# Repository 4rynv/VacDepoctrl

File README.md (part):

# VacDepoctrl — Vacuum Deposition Controller

A Raspberry Pi-based vacuum process controller. The current process is DC magnetron sputter deposition — chamber pump-down, argon gas flow, plasma ignition, and sputtering via a live Tkinter GUI with scrolling sensor graphs and a hardware-interlocked state machine. A thermal evaporation mode is planned as a second process on the same rig control stack.

---

## Table of Contents

- [Hardware Overview](#hardware-overview)
- [Software Architecture](#software-architecture)
- [File Structure](#file-structure)
- [State Machine](#state-machine)
- [Pressure Reference](#pressure-reference)
- [Installation](#installation)
- [Running](#running)
- [Remote GUI Access](#remote-gui-access)
- [Web Dashboard](#web-dashboard)
- [Simulation Mode](#simulation-mode)
- [Configuration](#configuration)
- [GUI Guide](#gui-guide)
- [Known Limitations](#known-limitations)
- [Roadmap](#roadmap)

---

## Hardware Overview

| Component | Model | Interface | Notes |
|---|---|---|---|
| Microcontroller | Raspberry Pi 5 (BCM GPIO) | — | Host for all control logic |
| Pirani gauge | ACE Instruments DHPG-015 | Analog 0–10V | Divided to 0–3.3V before ADC (ratio 0.33) |
| ADC | ADS1115 | **I2C bus 1** @ 0x48 | Pirani on A0 (divided), MFC feedback on A1 (divided), turbo RPM tach on A2 |
| MFC | MKS 1179A | Analog 0–5V setpoint | 0–700 sccm Argon |
| DAC | MCP4725 | **I2C bus 1** @ 0x60 | Level-shifted to the MFC's full 0–5V setpoint range — see below |
| DAC buffer | LM358P op-amp | Analog | Buffers + level-shifts the DAC output up to 0–5V; DAC alone cannot drive the MFC setpoint input |
| Turbo enable | Opto-isolator (4N35) | GPIO 17 (BCM, phys 11) | Marginal — needs BC547 output buffer, see below |
| MFC valve close | Emergency shut | GPIO 27 (BCM, phys 13) | Pulls MFC valve closed on demand |
| Turbo inlet valve | Relay via BC547 | **GPIO 22 (BCM, phys 15)** | HIGH = valve OPEN, LOW = valve CLOSED (relay NC contact) |
| Energy meter | PZEM-004T-100A | Modbus-RTU over CP2102 USB-TTL, `/dev/ttyUSB0` | AC voltage/current/power on the variac output; plasma-ignition sensing. **Optional at startup** — see below |

### Raspberry Pi pin connections

[Full 40-pin header and device wiring diagram](docs/pinout.md)

| Function | BCM GPIO | Physical header pin | Connection |
|---|---|---|---|
| I2C1 SDA | GPIO2 | **3** | ADS1115 SDA + MCP4725 SDA |
| I2C1 SCL | GPIO3 | **5** | ADS1115 SCL + MCP4725 SCL |
| Signal ground | — | **6** (or another GND) | ADC/DAC signal ground |
| Turbo enable | GPIO17 | **11** | Opto-isolator input circuit |
| MFC emergency close | GPIO27 | **13** | Existing MFC valve-close interface |
| Turbo inlet valve | GPIO22 | **15** | BC547 relay-driver input |

GPIO23/24 (physical pins 16/18) are no longer the I2C connection.

### I2C: Hardware Bus 1 on GPIO 2/3

The Pi 5 uses hardware I2C1 at 100 kHz. Configure `/boot/firmware/config.txt`:

```ini
dtparam=i2c_arm=on
dtparam=i2c_arm_baudrate=100000
```

| Signal | BCM | Physical pin |
|---|---|---|
| SDA | GPIO 2 | 3 |
| SCL | GPIO 3 | 5 |
| GND | Ground | 6 |

Connect both ADS1115 and MCP4725 to this bus; keep pull-ups at 3.3 V.
Power down before moving SDA/SCL from the previous GPIO23/24 wiring.
The code uses `ExtendedI2C(I2C_BUS_NUMBER)` with `I2C_BUS_NUMBER = 1`.
The older software-bus setup was a workaround for reported damaged GPIO2/3
on a previous setup; this configuration assumes functioning GPIO2/3.
Reboot after changing boot configuration; the operator performs device checks
and the first controller launch with equipment in a safe condition.

### Voltage Divider (Pirani Output)

The DHPG-015 outputs 0–10V. A 3-resistor voltage divider scales this to 0–3.3V for the ADS1115 (divider ratio 0.33). All pressure thresholds in `config.py` are expressed in post-divider (ADC-side) volts. The full manufacturer calibration table lives in `hardware/datasheets/Di-Hi-Pr-Pirani output voltage.pdf` and is transcribed as `_PIRANI_CAL` in `main.py`.

### DAC Output Buffer + Level Shifter (LM358P)

The MCP4725 cannot source enough current to drive the MFC setpoint input directly — above ~1.25V the output voltage collapses under load even though it reads correctly when unloaded. An LM358P stage buffers the DAC output and shifts it up to the MFC's full 0–5V setpoint range before it reaches the MFC (`ARGON_DAC_VREF = 5.0` in `config.py` reflects this — commanded flow covers the full 0–`MFC_FULL_SCALE` range, not a fraction of it):

```
DAC OUT ──────────────┬──── LM358 IN+ (pin 3)
                       │
                  (feedback) IN- (pin 2) ──── OUT (pin 1) ──── MFC setpoint
LM358 VCC (pin 8) ── Pi 5V
LM358 GND (pin 4) ── GND
```

Power the op-amp from the Pi's **5V** rail, not 3.3V. The diagram above shows the original current-buffer wiring; the gain-setting feedback network that shifts the output up to 0–5V isn't captured in this ASCII diagram.

### Turbo Inlet Valve (GPIO 22 → BC547 → Relay → Solenoid)

The turbo inlet solenoid valve (~50 mA @ 25–26 V) is switched by a relay, driven by a BC547:

```
GPIO22 ──470Ω── base   BC547   collector ── relay coil ── +5V
                          emitter ── GND         ▲
                                          1N4007 across coil
                                          (band toward +5V)

Valve circuit ── relay COM + NC contacts (isolated from the Pi)
```

- Valve is wired through the relay's **NC (normally closed)** contact: relay released = valve circuit shorted = **valve CLOSED**; relay energized = **valve OPEN**.
- Logic (in `_poll()`, `turbo_valve_step()`): valve held CLOSED at all times; **latched OPEN** during **VENTING** once turbo pump RPM (tach on ADC A2, see [Turbo Pump RPM](#turbo-pump-rpm-adc-a2)) sustains `TURBO_VALVE_CONFIRM_SAMPLES` consecutive reads at or below `TURBO_VALVE_OPEN_RPM_MAX` (35000 RPM); re-closed automatically on leaving VENTING. The debounce prevents a single corrupted I2C read from opening the valve; the latch prevents relay chatter once open. Driven by rotor speed directly rather than inferring it from chamber pressure — the earlier pressure-based gate (`TURBO_VALVE_OPEN_MBAR`) has been replaced.
- Fail-safe: if the Pi crashes or loses power, the relay releases and the valve **fails closed** — the safe direction for the turbo inlet.
- GUI shows live actuation state (`T-VALVE : CLOSED` / `OPEN (venting)`).

### Turbo Pump RPM (ADC A2)

- Tach/speed output, 0–3.3V linear = 0–90000 RPM (`TURBO_RPM_VOLTAGE_FULL_SCALE`, `TURBO_RPM_FULL_SCALE`), read by `TurboRPMController` (`turbo_rpm.py`) every poll tick regardless of state.
- Displayed in its own **Turbo Pump** panel (`T-RPM`, `T-RPM V`, a scrolling RPM graph, plus `OPTO` and `T-VALVE` state — both turbo-side actuators, moved here from the Pirani panel) — below the Plasma panel, beside the Pirani/MFC panels.
- During **VENTING**, once RPM drops to/below `VENTING_PUMP_OFF_PROMPT_RPM` (2000), the Pirani panel's status message turns orange and prompts the operator to turn off the primary/roughing pump — an early, informational cue, not a gate. The actual gate on completing the vent is separate — see [Vent Completion Confirmation](#vent-completion-confirmation) below.
- Feeds the turbo inlet valve interlock above and the cross-sensor checks below.

### Vent Completion Confirmation

Reaching atmospheric pressure during VENTING does **not** by itself complete the vent. Earlier, `sm.update()` transitioned `VENTING → IDLE` purely from Pirani voltage — but the turbo inlet valve closes the instant the state leaves VENTING (`turbo_valve_step()`), so that auto-transition could reclose the valve before the operator had any real chance to react to the "turn off the primary pump" cue above, let alone actually do it.

`VENTING → IDLE` is now owned exclusively by `_poll()` (the same ownership pattern as `ARGON_FLUSH → PLASMA_IGNITING`), gated by `vent_complete_ready()`: **both** atmospheric pressure **and** an explicit operator click are required.

- Once Pirani reaches `VENTING_COMPLETE_VOLTAGE` during VENTING, `_state["vent_complete_pending"]` latches True — the Pirani panel's status message turns red ("Atmosphere reached — turn OFF the primary/roughing pump, then click Confirm Pump Off") and a **Confirm Pump Off** button appears in Controls (hidden otherwise, same show/hide pattern as Clear Fault).
- Clicking it sets `_state["vent_complete_confirmed"]`; `_poll()` picks this up on its next tick and, if pressure is still at/above atmosphere, transitions to IDLE — closing the turbo inlet valve as part of the normal VENTING-exit path.
- Both flags reset on entering IDLE or VENTING (`handle_hardware_interlocks()`), so a stale confirmation from a previous cycle can never auto-complete the next one.

### Energy Meter (PZEM-004T-100A, plasma ignition sensing)

Reads AC voltage/current/power/energy/frequency/power-factor on the sputtering supply's **variac output** and uses the current-draw step when the discharge strikes to detect plasma ignition. Talks Modbus-RTU over a CP2102 USB-TTL adapter plugged into the Pi's USB port (`pzem_meter.py`) — a completely separate transport from the ADS1115/MCP4725 I2C bus above.

> [!warning] Mains AC hazard
> The PZEM's voltage-sense terminals and current-transformer (CT) clamp are on **live mains-derived AC**, not the Pi's low-voltage side. Work de-energized (variac and upstream breaker off), verify with a meter before touching any terminal, don't work alone, and don't exceed the CT's 100A rating. The PZEM's internal isolation protects the TTL/USB side from the AC side *once wired correctly* — it does not protect you while wiring it.

#### Wiring

**AC side (mains, de-energized while wiring):**

- Connect the PZEM's **L / N voltage-sense terminals directly across the variac's OUTPUT** (not its input) — the two wires feeding whatever the variac drives (typically an HV/isolation transformer feeding the sputtering cathode supply).
- Clamp the **split-core CT around the same variac output's live (L) conductor** — do not clamp both L and N together (their fields cancel and it reads ~0A), and do not clamp the input side.
- Wiring the CT and voltage sense to the *same* side (output) is required for the power reading to mean anything — the PZEM computes P = V × I × PF locally, so V and I must reflect the same node.
- This placement means voltage/current/power all read what's actually delivered to the sputtering supply, independent of the variac's own tap position — exactly the load signature that changes when the discharge strikes (impedance drop → current step).

**TTL side (isolated, low-voltage, safe to wire live):**

| PZEM TTL pin | CP2102 pin | Notes |
|---|---|---|
| 5V  | 5V  | PZEM-004T v3.0's TTL interface requires 5V — verify the CP2102's voltage-select jumper (if it has one) is set to 5V, not 3.3V |
| GND | GND | Common ground |
| TXD | RXD | Cross — PZEM transmits into the adapter's receive pin |
| RXD | TXD | Cross — PZEM receives from the adapter's transmit pin |

Plug the CP2102 into any Pi USB port. It enumerates as `/dev/ttyUSB0` (check with `ls /dev/ttyUSB*`; use a `/dev/serial/by-id/...` symlink instead if more than one USB-serial device is ever attached). The Pi user needs the `dialout` group to access it without root:

```bash
sudo usermod -a -G dialout $USER
# log out and back in for the group change to take effect
```

#### Protocol

Modbus-RTU, 9600 baud 8N1, factory-default slave address `0xF8`. `pzem_meter.py` hand-rolls the request framing and CRC16 (matching how `mfc_control.py` hand-rolls the MCP4725 I2C write) rather than pulling in a general Modbus library — reads input registers 0x0000–0x0009 (voltage, current, power, energy, frequency, power factor, alarm) every poll tick.

**Optional hardware, unlike the ADS1115/MCP4725 checked in `_startup_self_test()`:** this sensor may not be wired up yet. `PZEMController.read()` never raises — if the serial port can't be opened or the meter doesn't respond, it returns `ready=False` and a zeroed reading. `main.py`'s two PZEM cross-sensor checks (below) only evaluate `if e["ready"]`, so nothing they do can fire until the meter is actually installed and responding — deploying this code cannot regress a rig that doesn't have the PZEM wired yet.

#### Plasma Detection

`plasma_detect_step()` applies the same debounced ON/OFF hysteresis pattern as the turbo enable opto (`TURBOOPTO_ON/OFF_THRESHOLD`) to the PZEM's current reading: `PZEM_PLASMA_CURRENT_ON_A` (default 1.0A, **unvalidated placeholder**) held for `PZEM_PLASMA_CONFIRM_SAMPLES` (3) consecutive ticks latches `plasma_detected` True; it clears immediately below `PZEM_PLASMA_CURRENT_OFF_A` (0.6A). Like every other cross-sensor threshold in this repo, these must be bench-measured against the real supply's no-load vs. struck-plasma current before they mean anything.

`plasma_detected` drives the **Plasma** GUI panel (replacing the old placeholder) and the `PLASMA_IGNITING → SPUTTER_READY` confirmation, which now has three paths:

| Path | Trigger | Default |
|---|---|---|
| Manual | Operator clicks **Confirm Plasma** | Always available |
| Hybrid cue | Confirm Plasma button highlights green once `plasma_detected` is True during `PLASMA_IGNITING` — operator still clicks | Always on |
| Auto-confirm | Operator arms the **Auto-Confirm** toggle in the Plasma panel; while armed, a confirmed detection advances the state machine the same way a manual click would, via the same `_complete_plasma_confirmation()` path | **Off by default** |

Auto-confirm is an explicit operator opt-in, not the default, because `PZEM_PLASMA_CURRENT_ON_A` is unvalidated — the same reasoning as every other "unvalidated until confirmed on the bench" threshold in `config.py`. `PLASMA_IGNITING`'s own `PLASMA_IGNITION_TIMEOUT` abort-to-READY path is unchanged and still the fallback if neither manual nor auto-confirm fires.

#### Bring-up notes / troubleshooting

- **Board-specific terminal layout, not the generic datasheet.** On Aryan's board, the AC-side 4-terminal block is L / N (voltage sense, across variac output) and two CT-lead terminals — but the *position* of these on the physical block didn't match the generic PZEM-004T datasheet. The L line initially went to the board's 10A direct-pass-through terminal position instead of the 100A/CT-clamp position; moving it to the correct terminal (found via the board's own silkscreen, not the datasheet) fixed it. **Always read your specific board's silkscreen, not a generic online diagram.**
- **The PZEM's measurement MCU is powered from the AC L/N line itself**, not the TTL 5V header. Symptom if you wire TTL first and haven't energized L/N yet: CP2102 TX blinks (host is sending fine), PZEM never replies — looks like a dead unit but is just unpowered. Resolves once L/N is actually connected to live AC.
- **A struck-but-undetected plasma likely means the CT isn't sensing the load, not a threshold-tuning problem.** Hit 2026-07-12: operator visually confirmed plasma and clicked Confirm Plasma, `PLASMA_IGNITING → SPUTTER_READY` succeeded, then `pzem_plasma_absent_check()` force-shut-down 5s later with the PZEM reporting **0.00 A** the entire time. A true zero (not "some current below 1.0A") points at the sensor path, not calibration — most likely the CT clamp isn't actually installed on the load line yet (this repo's CT bring-up was still pending a bench test on the real variac-output load as of the prior session), or is clamped over both L and N together (fields cancel to ~0A), rather than L alone.
- **If real current draw is small relative to the CT's 100A rating, wind multiple turns of the live conductor through the clamp before closing it.** A CT senses ampere-*turns*, so *N* turns gives `N × I_actual` on the reading — useful because a 100A-rated core sensing a sub-1A sputtering load sits at the very bottom of its response curve, where accuracy/noise floor issues are common. Divide the reported current/power by *N* in software to recover the true value, or (simpler, since only the comparison matters) scale `PZEM_PLASMA_CURRENT_ON_A`/`_OFF_A` by *N* instead. Sanity-check the real current independently first (a separate clamp meter, or the sputtering supply's own front-panel readout) before deciding how many turns to use.

### Cross-Sensor Consistency Checks

Every threshold elsewhere in this doc compares one sensor to one fixed value. These instead compare two live readings to each other — catching a case where each reading is individually "in range" but the two together don't make physical sense. All feed the **global safety gate** below: a sustained flag forces a full hardware cutoff, not just a status message. Grace periods are placeholder defaults (favor fewer false positives over noise from normal settling time) — tune once measured against real spin-up/response/settling behavior on the bench. Because a false positive forces a real shutdown, treat these as unvalidated until confirmed on the bench.

| Check | Compares | Flags when | Config |
|---|---|---|---|
| `turbo_spinup_check()` | Turbo enable opto (GPIO 17) vs turbo RPM (ADC A2) | Opto commanding the turbo on for `TURBO_SPINUP_GRACE_SECONDS` (60s) while RPM stays below `TURBO_RPM_STALL_THRESHOLD` (10000) — turbo/RPM-sensor/wiring fault, or the turbo never spun up at all | `config.py` |
| `turbo_rpm_drop_check()` | Same opto/RPM pair, but tracks a confirmed-healthy peak | RPM has exceeded `TURBO_RPM_STALL_THRESHOLD` at least once (confirmed healthy spin), then drops back below it for `TURBO_RPM_DROP_GRACE_SECONDS` (10s) while opto is still on — a running turbo failing/degrading, distinct from "never spun up" | `config.py` |
| `mfc_flow_check()` | Commanded flow (DAC/`flow_target`) vs measured flow (A1 feedback) | Commanded ≥ `MFC_FLOW_MIN_COMMANDED_SCCM` (20) but measured stays below `MFC_FLOW_RESPONSE_FRACTION` (0.2×) of commanded for `MFC_FLOW_GRACE_SECONDS` (5s) — MFC not responding, dead unit, or empty gas supply | `config.py` |
| `dac_saturation_flow_check()` | DAC output voltage vs measured flow | DAC pegged within `DAC_SATURATION_MARGIN_V` (0.1V) of `ARGON_DAC_VREF` while measured flow stays below `DAC_SATURATION_FLOW_FRACTION` (0.5×) of `MFC_FULL_SCALE`, for `DAC_SATURATION_GRACE_SECONDS` (10s) — the PID has given up on proportional correction and is commanding max output with nothing coming back: stuck valve, blocked line, or empty supply. A stronger signal than `mfc_flow_check` alone | `config.py` |
| `pressure_convergence_check()` | Current Pirani voltage vs the active PID target (flush/sputter) | `\|current - target\|` exceeds `PRESSURE_CONVERGENCE_TOLERANCE_V` (0.3V) for `PRESSURE_CONVERGENCE_GRACE_SECONDS` (90s) despite the control loop running — leak, stuck valve, or MFC fault. Raised from 20s after a bench run showed a legitimate large setpoint step (e.g. PLASMA_IGNITING → SPUTTER_READY) needs longer than that to converge given the deliberately gentle PID tuning | `config.py` |
| `pzem_plasma_absent_check()` | Process state (SPUTTER_READY/SPUTTERING only) vs PZEM `plasma_detected` | In SPUTTER_READY or SPUTTERING — both assume plasma is already lit — with no PZEM-confirmed current draw for `PZEM_PLASMA_ABSENT_GRACE_SECONDS` (5s): an arc dropout or the plasma extinguishing mid-run. PLASMA_IGNITING is deliberately excluded (`PLASMA_IGNITION_TIMEOUT` already owns "never struck"). Only evaluated once the PZEM is `ready` — see Energy Meter section above | `config.py` |
| `pzem_power_unexpected_check()` | Process state (everywhere except PLASMA_IGNITING/SPUTTER_READY/SPUTTERING) vs PZEM `plasma_detected` | Plasma-level current draw while nowhere near attempting ignition (IDLE/PUMP_DOWN/READY/ARGON_FLUSH/VENTING) for `PZEM_POWER_UNEXPECTED_GRACE_SECONDS` (5s) — stuck relay, live supply, or wiring fault. Only evaluated once the PZEM is `ready` | `config.py` |

All are pure functions (`main.py`, next to `turbo_valve_step()`) — no I/O, no wall-clock access internally (the current timestamp is passed in), so they're tested directly like the calibration/valve logic.

### Global Safety Gate

Everything above this point in the doc is a *local* mechanism: a specific check for a specific failure, conditioned on which state you're in. The global gate is different — evaluated every poll tick **regardless of current state**, and any single condition tripping it forces the exact same full cutoff: turbo valve closed (direct GPIO write), MFC flow/valve/opto off, state forced to IDLE (`sm.emergency_stop()`), **and the trip latches** (see below).

| Condition | Detects | Config |
|---|---|---|
| Sustained cross-sensor flag | Any of the checks above, once their own grace period elapses | see table above |
| `sensor_range_check()` | Any ADC-derived voltage (Pirani, MFC feedback, turbo tach) outside `SANE_VOLTAGE_MIN`/`SANE_VOLTAGE_MAX` for `SENSOR_RANGE_CONFIRM_SAMPLES` (5) consecutive ticks — disconnected, shorted, or miswired sensor, not a legitimate reading at any pressure/flow/speed. Suppressed for `STARTUP_GRACE_SECONDS` (5s) after the poll loop starts — real analog settling transients (MFC feedback observed at -0.15 to -0.23V for a few seconds after power-on) tripped this otherwise | `config.py` |
| Consecutive poll-loop exceptions | `CONSECUTIVE_EXCEPTION_LIMIT` (5) ticks in a row raise — occasional I2C/EMI glitches are tolerated (as before), but this many in a row is a real fault, not noise. Also suppressed during `STARTUP_GRACE_SECONDS` | `config.py` |
| Heartbeat / watchdog | The GUI thread (`_refresh()`) checks `_state["last_tick"]`; if the poll loop hasn't updated it within `HEARTBEAT_TIMEOUT_SECONDS` (2.0s), the poll thread is presumed stalled/hung. Checked from the GUI thread specifically — a hung poll thread can't detect its own hang | `config.py` |

All of this routes through `_force_safe_shutdown(reason)` (`main.py`) — safe to call every tick for as long as a condition persists (GPIO/state-machine calls are idempotent; `_set_error()` de-dupes the repeated log line rather than spamming it). `handle_hardware_interlocks()`'s own mfc/pirani cutoffs are already exception-safe (`SputterStateMachine` catches callback errors internally), so the only extra guarding needed is around the direct turbo-valve GPIO write, in case the poll thread hung mid-I2C-transaction.

**The trip latches — a bench run found why this matters.** `emergency_stop()` alone forces IDLE, but IDLE's own auto-resume-to-PUMP_DOWN logic (`_poll()`) will immediately re-enter PUMP_DOWN if pressure is already low (e.g. an external roughing pump already has the chamber down) — silently undoing the shutdown within one tick, with the process continuing as if nothing happened. `_force_safe_shutdown()` now sets `_state["safety_tripped"]`, which blocks that auto-resume and shows a red banner + "Clear Fault" button in the Process State panel, plus a one-time modal alert. The IDLE branch checks this flag before its auto-transition. Clearing does **not** reset the underlying check's own "since" timer — if the root cause is still present, it re-trips immediately on the next tick. That's intentional: acknowledging a fault without fixing it must not let the process quietly continue.

### Startup Self-Test

Runs once before the poll thread starts (`_startup_self_test()`, `main.py`): re-validates config invariants at runtime (`config_sanity_failures()` — same checks as `TestConfigSanity`, but live, so a bad future edit to `config.py` is caught before the app runs with a broken safety threshold; this is exactly the class of bug that shipped once, `VENTING_COMPLETE_VOLTAGE` at ~5 mbar instead of near-atmosphere), and confirms the ADS1115 and MCP4725 DAC actually ACK on the I2C bus. Any failure prints to console and exits — no GUI exists yet at this point in startup.

### Persistent Event Log

Every operator-visible error/warning and every state transition is appended to `sputter_ctrl.log` (next to `main.py`, `EVENT_LOG_FILENAME` in config) via `_log_event()` — the GUI status bar only shows the latest message and auto-expires it after `ERROR_DISPLAY_SECONDS`, so this is the only place an incident can be reconstructed after the fact. `_set_error()` is the single choke point every error message goes through (writes `_state["error"]` and logs, de-duping repeats); `handle_hardware_interlocks()` logs every transition unconditionally, regardless of which state it's entering.

Do **not** drive relay coils or solenoids from a 4N35 directly — see the hard-won rule below.

### Opto/Load Rule of Thumb (learned the expensive way)

A 4N35's usable output current is roughly `CTR (~100%) × LED current (~10 mA max from a GPIO)` ≈ **10 mA**. Asked for more, it goes linear and drops the supply across itself (looks like a mystery series resistor). Loads measured on this rig:

| Load | Draw | 4N35 alone? |
|---|---|---|
| Turbo enable input | ~15–30 mA | **No** — needs BC547 buffer (pending) |
| Relay coil (5V) | ~60 mA | No — driven by BC547 directly, opto not needed (relay contacts provide the isolation) |
| Inlet solenoid | ~50 mA @ 26V | No — relay contacts switch it |

The turbo enable opto (GPIO 17) currently only works with excess LED drive; the proper fix is a BC547 buffer on its output (opto pin 5 → enable+, pin 4 → BC547 base, 10 kΩ base–emitter, BC547 C/E across the enable terminals). Flyback diodes go **in parallel across coils** (reverse-biased), never in series.

---

## Software Architecture

```
main.py
├── Hardware init (GPIO, ExtendedI2C bus 1, ADS1115)
├── Shared state dict (thread-safe, _lock)
├── Polling thread (_poll) — runs every POLLING_INTERVAL (0.2s)
│   ├── Reads Pirani + MFC + turbo RPM (A2) + PZEM (variac current) sensors
│   ├── Drives MFC pressure PID loop
│   ├── Drives turbo inlet valve latch (GPIO 22), gated on turbo RPM (not pressure)
│   ├── Debounced plasma_detect_step() from PZEM current -> plasma_detected
│   ├── Auto-confirms PLASMA_IGNITING -> SPUTTER_READY if the operator has
│   │   armed Auto-Confirm and plasma_detected is True
│   ├── Calls sm.update() for auto-transitions
│   ├── Converts Pirani voltage <-> mbar via log-linear calibration table
│   ├── End-of-tick safety cutoff re-assert (E-STOP race guard)
│   └── Updates shared state dict
├── Tkinter GUI (main thread)
│   ├── _refresh() — runs every GUI_REFRESH_INTERVAL (200ms) via root.after()
│   ├── Scrolling graphs (ScrollingGraph)
│   ├── Live pressure readout in mbar (adc_voltage_to_mbar)
│   ├── Manual set-point entry fields (sputter target mbar, argon PSI)
│   ├── Error display with ERROR_DISPLAY_SECONDS auto-expiry
│   └── Button callbacks → shared _try_*() operator commands
├── Web dashboard server (daemon threads — web_ui.py, see Web Dashboard)
│   ├── GET /events — SSE stream of _state snapshots to each browser
│   └── POST /command — dispatches the SAME _try_*() operator commands
└── Hardware interlock callback
    └── handle_hardware_interlocks() — fires on every state transition
```

The polling thread and GUI thread never share objects directly — all data passes through `_state` dict protected by `_lock`. On window close, `_stop_event` is set and the polling thread is **joined** (2 s timeout) before hardware shutdown and `GPIO.cleanup()`.

**E-STOP race guard:** the poll loop reads the state once per tick; if an E-STOP/vent transition lands mid-tick, the interlock callback's cutoff could be overwritten by in-flight `valve_release()`/`set_flow()` calls. The poll loop therefore re-asserts the full safety cutoff at the end of any tick in which the state machine moved to IDLE/VENTING — the cutoff is always the last hardware write of the tick.

**Error handling:** errors are no longer cleared by the polling loop each tick. They persist in the status bar for `ERROR_DISPLAY_SECONDS` (10 s) and then auto-expire, so both operator-guard messages and the plasma-timeout message are actually readable.

---

## File Structure

```
VacDepoctrl/
├── main.py            — Entry point: GUI, polling thread, hardware init, cal table
├── config.py          — All constants, thresholds, and pin assignments
├── state_machine.py   — SputterStateMachine class (future: per-process state machines)
├── drivers/           — one class per hardware device
│   ├── mfc_control.py — MFCController class (DAC, valve, PID loop)
│   ├── pirani.py      — PiraniController class (ADC, turbo enable opto)
│   ├── turbo_rpm.py   — TurboRPMController class (ADC A2 tach → RPM)
│   └── pzem_meter.py  — PZEMController class (PZEM-004T-100A, Modbus-RTU over USB-TTL)
├── ui/
│   ├── graph.py       — ScrollingGraph class (pure Tkinter, no matplotlib; single/dual/multi-series)
│   ├── web_ui.py      — browser dashboard server (stdlib HTTP + SSE), parallel to the Tkinter GUI
│   └── web/
│       └── index.html — the dashboard page (self-contained: inline CSS/JS, no CDN)
├── sim/
│   └── sim_hardware.py — ChamberSim + fake hardware modules for SPUTTER_SIM=1 (Simulation Mode)
├── hardware/
│   ├── Raspi_HAT/     — KiCad project for the custom Raspberry Pi HAT (schematic/PCB/BOM)
│   └── datasheets/    — Pirani gauge output-voltage table PDF
├── docs/              — GUI screenshot and other README assets
├── assets/            — desktop/app icon source (app-icon*.png, AppIcon.icns)
├── scripts/
│   ├── setup.sh       — venv + dependency installer, also installs the desktop launcher
│   ├── VacDepoctrl.desktop       — desktop launcher icon (installed by setup.sh; see Installation)
│   ├── setup_remote_gui_macos.sh — one-time XQuartz setup, see Remote GUI Access
│   └── build_mac_launchers.sh    — builds the VacDep Remote.app / VacDep Simulation.app Desktop icons
└── tests/
    ├── adc_test.py         — ADS1115 read loop (bus 1)
    ├── dac_test.py         — MCP4725 sweep + readback (bus 1)
    ├── opto_test.py        — GPIO 17 turbo enable opto toggle
    ├── turbo_valve_test.py — GPIO 22 relay/valve toggle
    ├── pzem_test.py        — PZEM-004T-100A live reading loop (USB-TTL)
    └── unit/               — hardware-free unit suite (fakes.py + test_all.py)
```

---

## State Machine

### States and Transitions

```
                    pressure rises
         ┌─────────────────────────────┐
         ▼                             │
       IDLE ──(pressure drops)──► PUMP_DOWN ──(vacuum reached + opto)──► READY
         ▲                             │                                     │
         │                    pressure rises                        [Start Argon Flush]
         │                             │                                     ▼
         └─────────────────────────────┘                            ARGON_FLUSH
                                                                         │
                                                              (0.09 mbar reached)
                                                                         ▼
                                                               PLASMA_IGNITING
                                                              │              │
                                                   [Confirm Plasma]    (2 min timeout)
                                                              │              │
                                                              ▼              ▼
                                                        SPUTTER_READY     READY
                                                              │
                                                       [Start Sputter]
                                                              ▼
                                                          SPUTTERING
                                                              │
                                                       [Stop Sputter]
                                                              ▼
                                                          VENTING
                                                              │
                                                (3.0V atmosphere) + [Confirm Pump Off]
                                                              ▼
                                                            IDLE

         Any state ──[Vent]──► VENTING ──(3.0V Pirani + Confirm Pump Off)──► IDLE
         Any state ──[E-STOP]──► IDLE (immediate hardware cutoff, latched — Clear Fault to resume)
```

### Automatic Transitions

| From | To | Condition | Where |
|---|---|---|---|
| `IDLE` | `PUMP_DOWN` | Pirani voltage ≤ 2.71V (10 mbar) | `_poll()` |
| `PUMP_DOWN` | `IDLE` | Pirani voltage ≥ 2.71V (pump failure/leak) | `_poll()` + `sm.update()` |
| `PUMP_DOWN` | `READY` | Voltage ≤ 0.3V AND opto enabled | `sm.update()` |
| `READY` | `PUMP_DOWN` | Pirani voltage ≥ 2.71V (pressure degraded) | `sm.update()` |
| `ARGON_FLUSH` | `PLASMA_IGNITING` | Voltage ≥ 1.287V (0.09 mbar) | **`_poll()` only** — sole owner: arms the ignition timeout and fires `_ignite_plasma()` |
| `PLASMA_IGNITING` | `READY` | 120s timeout, no plasma confirmation | `_poll()` |
| `PLASMA_IGNITING` | `SPUTTER_READY` | PZEM confirms plasma-level current draw, **only if the operator has armed Auto-Confirm** | `_poll()` — see [Energy Meter](#energy-meter-pzem-004t-100a-plasma-ignition-sensing) |
| `VENTING` | `IDLE` | Pirani voltage ≥ 3.0V (near-atmosphere) **AND** operator has clicked Confirm Pump Off | **`_poll()` only** — see [Vent Completion Confirmation](#vent-completion-confirmation) |

`PLASMA_IGNITING → SPUTTER_READY` is **operator-driven by default** (Confirm Plasma button, highlighted once the PZEM confirms detection) with an explicit opt-in **Auto-Confirm** toggle for the sensor-driven path — see the Energy Meter section for why auto-confirm defaults off. `VENTING → IDLE` similarly requires an explicit operator click regardless of pressure — there is no auto-confirm option for this one, since it's gating a real physical action (turning off the primary pump), not just a detection threshold.

### Manual Transitions (Operator Buttons)

| Button | Transition | Guard |
|---|---|---|
| Start Argon Flush | `READY → ARGON_FLUSH` | Argon inlet ≥ 15 psi |
| Confirm Plasma | `PLASMA_IGNITING → SPUTTER_READY` | None |
| Start Sputter | `SPUTTER_READY → SPUTTERING` | Argon inlet ≥ 15 psi |
| Stop Sputter | `SPUTTERING → VENTING` | None |
| Vent | `PUMP_DOWN`, `READY`, `ARGON_FLUSH`, `PLASMA_IGNITING`, `SPUTTER_READY`, `SPUTTERING` → `VENTING` | None — `PUMP_DOWN` added 2026-07-12 (previously only `IDLE→PUMP_DOWN→IDLE` was reachable from PUMP_DOWN; vent is now available mid-pump-down too) |
| Confirm Pump Off | `VENTING → IDLE` | Only appears once atmosphere is reached; see [Vent Completion Confirmation](#vent-completion-confirmation) |
| E-STOP | Any → `IDLE` | None — immediate. Routes through `_force_safe_shutdown()`: closes the turbo valve by direct GPIO write (no dependency on the poll thread being alive) and **latches** — Clear Fault required to resume, like a real EMO reset |

### Hardware Interlock Callback

`handle_hardware_interlocks()` fires synchronously on every state transition:

- **→ IDLE or VENTING**: `mfc.set_flow(0)`, `mfc.valve_close()`, `pirani.set_opto(False)`, and resets `plasma_ignition_start` / `plasma_ignition_triggered` so the next flush cycle starts clean (a stale flag previously could leave PLASMA_IGNITING with no armed timeout)
- **→ PUMP_DOWN**: `pirani.set_opto(False)` — resets opto for next pump-down cycle

During VENTING the poll loop additionally holds the MFC valve **closed** every tick (venting is done with the turbo inlet valve, not through the MFC).

---

## Pressure Reference

All voltages are post-divider (ADC input, ×0.33 from raw gauge output). Conversion between Pirani voltage and mbar uses **log-linear interpolation** against the full manufacturer calibration table (`_PIRANI_CAL` in `main.py`, source PDF in `hardware/datasheets/`): linear in voltage, logarithmic in pressure, matching the gauge's thermal-conductivity response. Both directions are implemented (`mbar_to_adc_voltage`, `adc_voltage_to_mbar`) and round-trip to machine precision at all 51 table points.

| Pressure (mbar) | Raw gauge (V) | ADC input (V) | Significance |
|---|---|---|---|
| 999 | 10.00 | 3.30 | Atmosphere (ADC saturated) |
| ~213 | — | 3.0 | `VENTING_COMPLETE_VOLTAGE` — VENTING → IDLE (safety margin below the 3.30V atmosphere point so the transition reliably fires) |
| 10 | 8.20 | 2.706 | `IDLE_PRESSURE_MAX_VOLTAGE` — pump-down gate |
| 0.09 | 3.90 | 1.287 | `ARGON_FLUSH_TARGET_VOLTAGE` — plasma ignition pressure |
| ~0.183 | 4.24 | 1.4 | Turbo enable opto fires (PUMP_DOWN, transition-based; raised from 1.3V 2026-07-12) |
| ~0.0057 | 0.91 | 0.3 | `PUMP_DOWN_COMPLETE_VOLTAGE` — PUMP_DOWN → READY gate (raised from 0.2V 2026-07-12) |
| 0.007 | 1.10 | 0.363 | 0.007 mbar — default sputtering pressure |

The GUI displays live pressure in mbar (bold, under the voltage readout), computed via `adc_voltage_to_mbar()`; reads `ATM (>999 mbar)` at ADC saturation.

### Sputter Target Pressure (operator-settable)

An input field sets the SPUTTER_READY / SPUTTERING target pressure directly in mbar (default 0.007). Entered values are converted to an ADC voltage target via the calibration table before being passed to `pressure_control_step()`.

Validated at entry: must be `> 0` and `≤ SPUTTER_TARGET_MAX_MBAR` (0.05 mbar). Values above the cap are rejected with a warning dialog rather than silently accepted — this also catches an Argon PSI value (tens) fat-fingered into this field, since any such value is far above the cap. Similarly, the Argon PSI field rejects anything below `ARGON_PRESSURE_MIN_PSI` (15 psi) with a warning, catching a Sputter P mbar value entered in the wrong field.

### Turbo Enable Opto Logic (GPIO 17)

Transition-based, not level-based:

- Goes **HIGH** the first time Pirani voltage drops below **1.4V** during `PUMP_DOWN` (raised from 1.3V 2026-07-12)
- Once set, stays HIGH until any state transition resets it via the interlock callback
- This prevents opto chatter on noisy ADC readings near the threshold
- Separate from `TURBOOPTO_ON_THRESHOLD`/`TURBOOPTO_OFF_THRESHOLD` in `config.py` (ADC-count based, ~1.31V/~1.87V) — those drive `pirani.py`'s `auto_opto=True` hysteresis path used in READY/ARGON_FLUSH, a different code path from this PUMP_DOWN transition-based one. The two are not currently kept in sync; only the PUMP_DOWN threshold above was changed this session.

---

## Installation

### 1. Clone the Repository

```bash
ssh av@<pi-ip>
git clone https://github.com/<your-username>/VacDepoctrl.git ~/VacDepoctrl
cd ~/VacDepoctrl
```

### 2. Enable Hardware I2C

Wire physical pins 3/5 as described above. Enable these settings under `[all]`
in `/boot/firmware/config.txt`, removing any old `i2c-gpio` overlay:

```ini
dtparam=i2c_arm=on
dtparam=i2c_arm_baudrate=100000
```

The operator should reboot when safe, then verify `/dev/i2c-1` exists.
Hardware verification should find ADS1115 at 0x48 and MCP4725 at 0x60.
Do not launch the controller until the wiring and equipment are ready:
`main.py` configures outputs immediately and can automatically enter PUMP_DOWN.

### 3. Run the Setup Script

```bash
cd ~/VacDepoctrl
chmod +x scripts/setup.sh
./scripts/setup.sh
```

This installs `adafruit-blinka`, `adafruit-circuitpython-ads1x15`, `adafruit-extended-bus`, `rpi-lgpio` (providing the `RPi.GPIO` API), and `pyserial` into a venv at `~/VacDepoctrl/venv/`, adds a `source_vacdep` alias to `~/.bashrc`, and places a **VacDepoctrl** icon on the desktop (`VacDepoctrl.desktop`) — double-click it to launch `main.py` directly, no terminal needed. First launch may need a one-time "Allow Launching" confirmation (right-click the icon → Allow Launching) depending on the desktop environment's trust settings for new `.desktop` files.

```bash
source ~/.bashrc
source_vacdep
```

### 4. (Optional) Energy Meter Serial Permissions

If the PZEM-004T-100A / CP2102 is wired up (see [Energy Meter](#energy-meter-pzem-004t-100a-plasma-ignition-sensing)), add the Pi user to `dialout` so `main.py` can open `/dev/ttyUSB0` without root:

```bash
sudo usermod -a -G dialout $USER
# log out and back in for the group change to take effect
```

This step can be skipped entirely — the meter is optional hardware and `main.py` starts normally without it (see `pzem_meter.py`).

---

## Running

Must be run on the Pi with a display connected (HDMI or VNC), not over a plain SSH session.

```bash
source_vacdep
cd ~/VacDepoctrl
python main.py
```

> Note: use `python`, not `python3`, inside the activated venv on this setup.

To run over SSH with display forwarding:

```bash
ssh -X av@<pi-ip>
source_vacdep && cd ~/VacDepoctrl && python main.py
```

This renders the GUI on your own machine instead of the Pi's local display —
see [Remote GUI Access](#remote-gui-access) below for one-time setup and why
you'd want to.

Bench-test scripts (run these with `main.py` stopped — they fight over pins):

```bash
python tests/adc_test.py          # live ADC readings, both channels
python tests/dac_test.py          # DAC voltage staircase + register readback
python tests/opto_test.py         # GPIO 17 toggle every 5 s
python tests/turbo_valve_test.py  # GPIO 22 relay/valve toggle every 5 s
```

---

## Remote GUI Access

**Why**: Raspberry Pi OS Bookworm's default desktop uses a Wayland compositor
(`labwc`). On older/weaker boards that compositor can
alone consume most of the CPU just keeping the desktop alive — independent of
`main.py` — which shows up as system-wide lag, including the mouse cursor
itself stuttering. Tkinter also doesn't speak Wayland natively; on this
desktop it runs through an `Xwayland` compatibility shim that gets composited
by `labwc` anyway, adding a second layer of overhead on top.

SSH X11 forwarding (`ssh -X`) sidesteps all of that: `main.py` still runs
*on* the Pi (it has to — that's where the GPIO/I2C/PZEM-over-USB hardware
physically is), but the X11 *protocol* (drawing commands, not rendered
frames) is tunneled to an X server running on your own machine, which does
the actual rendering. None of the Pi's local compositor is involved. This is
optional — if you're on the Pi's physical HDMI display or VNC and it isn't
laggy for you, there's nothing to set up.

The Pi side needs no configuration — `sshd` already has `X11Forwarding yes`
and `xauth` installed. Every OS below needs its own X server to *receive*
the forwarded connection, since none of them speak X11 out of the box.

### macOS

```bash
./scripts/setup_remote_gui_macos.sh
```

Or manually:

```bash
brew install --cask xquartz
open -a XQuartz
```

Then from a **new** terminal (so it picks up XQuartz's environment):

```bash
ssh -X av@<pi-ip>
source_vacdep && cd ~/VacDepoctrl && python main.py
```

If the window doesn't appear, try `-Y` (trusted forwarding, fewer
restrictions) instead of `-X`. Still nothing? As a last resort:

```bash
defaults write org.macosforge.xquartz.X11 nolisten_tcp -bool false
```

then quit and relaunch XQuartz. This allows raw TCP connections to the X
server, not just the local Unix socket `ssh -X` normally uses — a real
(if small, loopback-only-by-default) security tradeoff, so it's not applied
automatically by the script above; only turn it on if the standard path
above doesn't work.

**Desktop launcher (optional):** once XQuartz is set up, `./scripts/build_mac_launchers.sh`
builds two double-clickable `.app` icons on the Desktop — the Mac
equivalent of `VacDepoctrl.desktop` on the Pi:

- **VacDep Remote.app** — picks a rig from a small known-rigs list baked
  into the app (edit `RIGS` in `scripts/build_mac_launchers.sh` and rebuild
  to add more — one entry auto-connects with no prompt, several show a
  choose-from-list dialog), then runs the `ssh -X` command above for you.
  Connects via the Pi's mDNS hostname (`av.local`) rather than a raw IP —
  DHCP has moved this rig's address before, but the mDNS name survives
  that. The SSH password itself is left to `ssh`'s own normal interactive
  Terminal prompt (secure, no extra tooling) rather than something like
  `sshpass`.
- **VacDep Simulation.app** — runs Simulation Mode locally (see below);
  no Pi or XQuartz-to-Pi connection needed, just XQuartz itself.

Both open Terminal.app rather than running silently, since `main.py`'s
startup self-test prints failures to the console before any GUI window
exists — same reasoning as `Terminal=true` in the Pi's `.desktop` file.
First launch of either needs a one-time right-click → Open to bypass
Gatekeeper's unsigned-app warning.

> [!note] Live network discovery was tried and doesn't work here
> mDNS *service* browsing (`dns-sd -B _ssh._tcp`) was the first approach
> tried for "find the Pi automatically" — it doesn't find this rig, since
> Avahi on the Pi isn't advertising `_ssh._tcp` (only plain hostname
> resolution works, which is what `av.local` above relies on). A maintained
> list is simply more reliable than scanning here.

### Windows

Two options — pick one:

- **MobaXterm** (recommended — simplest, one tool): install it, open a new
  SSH session to the Pi. X11 forwarding is enabled by default; its bundled
  X server starts automatically.
- **VcXsrv + PuTTY**: install VcXsrv, run **XLaunch** with *"Disable access
  control"* checked and leave it running, then in PuTTY set
  **Connection → SSH → X11 → Enable X11 forwarding** (X display location
  `localhost:0`) before connecting.

Either way, once connected: `source_vacdep && cd ~/VacDepoctrl && python main.py`.

### Linux

Usually nothing to install. A native X11 desktop session supports `ssh -X`
out of the box; a Wayland desktop on Linux ships `Xwayland` by default too
(unlike macOS/Windows, which have no X server at all). Just:

```bash
ssh -X av@<pi-ip>
source_vacdep && cd ~/VacDepoctrl && python main.py
```

---

## Web Dashboard

Any browser on the LAN gets the full live interface — readouts, graphs, and
controls — at:

```
http://av.local:8080          (or http://<pi-ip>:8080)
```

No app, no XQuartz, no SSH, no per-OS setup; works from a phone. Served by
`ui/web_ui.py` (stdlib HTTP + Server-Sent Events — nothing to install) with the
page in `ui/web/index.html` (self-contained, no CDN: renders on a LAN with no
internet).

**Parallel by design, never a replacement.** The web dashboard is a second
*view* of the same running `main.py` — the local Tkinter GUI always runs
regardless (`WEB_UI_ENABLED` only controls the browser side). A network
problem can therefore only ever cost the browser page; the control loop and
the local GUI on the rig don't know or care whether anyone is connected. The
page makes staleness unmissable: if the stream stops for >3 s it greys out
behind a DISCONNECTED banner rather than silently showing frozen numbers.

**Commands are the same code path as the local buttons.** Every browser
action dispatches the exact `_try_*()` function the corresponding Tkinter
button calls — same argon-pressure guards, same state-machine locks, same
confirmation gates (Confirm Plasma, Confirm Pump Off, Clear Fault). Every
web command is appended to `sputter_ctrl.log` with the client's IP, so the
audit trail records who did what from where.

> [!warning] No authentication
> Anyone on the LAN who can reach port 8080 can operate the rig — the same
> trust model as the Pi's own VNC/SSH access. Don't expose the Pi to a
> network you don't control; set `WEB_UI_ENABLED = False` in `config.py` to
> not open the port at all.

Troubleshooting: browsers with **HTTPS-Only mode** (Firefox especially)
rewrite a bare `<ip>:8080` to `https://` and fail with
`SSL_ERROR_RX_RECORD_TOO_LONG` — the server is plain HTTP, so the URL must
start with an explicit `http://`. The Tkinter header shows the full URL in a
selectable field with a Copy button for exactly this reason.

> [!warning] Deploy this feature as a set, not piecemeal
> `WEB_UI_ENABLED` lives in `config.py`, but the code it depends on
> (`ui/web_ui.py`, `ui/web/index.html`) are separate files. A partial `scp` that
> ships a `config.py` with `WEB_UI_ENABLED = True` but not the other two
> crashes `main.py` on startup with `ModuleNotFoundError: No module named
> 'web_ui'` — **every** launch path fails identically (desktop icon, SSH -X,
> plain SSH), since the crash happens at import time before Tkinter ever
> gets a chance to open a window. Hit and fixed 2026-07-12. Always deploy
> `config.py` together with the whole `ui/` folder, or set
> `WEB_UI_ENABLED = False` on the Pi if you're deliberately deploying
> without the dashboard for now.

---

## Simulation Mode

Runs the full GUI and control loop — state machine, PID loop, cross-sensor
checks, plasma detection — on any machine with no Pi, no sensors, and no
GPIO/I2C/serial hardware attached. Useful for developing/demoing this
project, or just poking at the UI without risking anything.

```bash
SPUTTER_SIM=1 python main.py
# or
python main.py --sim
```

`sim/sim_hardware.py` installs fake `RPi.GPIO` / `adafruit_ads1x15` /
`adafruit_extended_bus` / `serial` modules into `sys.modules` before
`main.py`'s own hardware imports run (the same technique the hardware-free
test suite uses) — but unlike the test suite's static, manually-set values,
these are backed by a live physics model (`ChamberSim`) that reacts to
whatever the real control loop actually commands: turbo RPM ramps when the
enable opto goes high, pressure falls while pumping and rises when the
turbo valve opens or the MFC commands flow, MFC measured flow chases
commanded flow with a lag, etc. The window shows an unmissable orange
"SIMULATION MODE" banner so it's never confused with a real run.

**Plasma strikes are manual, not automatic.** An early version auto-triggered
the simulated variac current from a flow+low-pressure heuristic, but that
fired during ARGON_FLUSH itself — before any real ignition attempt, since
the PID legitimately drives flow/pressure into the same range just
converging on the flush target. `_ignite_plasma()` is still a stub on real
hardware too, so nothing should auto-decide this in the simulation either.
Instead, Simulation Mode adds a **"Plasma Strike (SIM)"** toggle button to
the Controls panel — click it whenever you want to simulate the plasma
actually igniting; it stays exactly as set until toggled again.

On macOS, `./scripts/build_mac_launchers.sh` builds a double-clickable
**VacDep Simulation.app** — see [Remote GUI Access](#remote-gui-access) above.

---

## Configuration

All tunable parameters are in `config.py`. Key constants:

```python
# I2C
I2C_BUS_NUMBER               = 1       # hardware I2C1 on GPIO2/3
ADS1115_I2C_ADDRESS          = 0x48
ARGON_DAC_I2C_ADDRESS        = 0x60

# GPIO (BCM)
GPIO_PIRANI_PIN              = 17      # turbo enable opto
GPIO_MFC_VALVE_CLOSE_PIN     = 27      # emergency valve close
GPIO_TURBO_VALVE_PIN         = 22      # turbo inlet valve relay (was GPIO 4 — dead pad)

# Pressure thresholds (post-divider volts unless noted)
IDLE_PRESSURE_MAX_VOLTAGE    = 2.71    # 10 mbar  — pump-down gate
PUMP_DOWN_COMPLETE_VOLTAGE   = 0.3     # PUMP_DOWN → READY gate
ARGON_FLUSH_TARGET_VOLTAGE   = 1.287   # 0.09 mbar — plasma ignition pressure
VENTING_COMPLETE_VOLTAGE     = 3.0     # VENTING → IDLE threshold (near-atmosphere; see Pressure Reference)
SPUTTER_TARGET_MAX_MBAR      = 0.05    # cap on the operator-settable Sputter P field
ARGON_PRESSURE_MIN_PSI       = 15.0    # floor on the operator-settable Argon PSI field

# Turbo pump RPM (tach on ADC A2) and inlet valve interlock
ADC_CHANNEL_TURBO_RPM        = 2
TURBO_RPM_VOLTAGE_FULL_SCALE = 3.3     # volts at A2 for full-scale RPM
TURBO_RPM_FULL_SCALE         = 90000.0 # RPM at full-scale voltage
TURBO_VALVE_OPEN_RPM_MAX     = 35000   # inlet valve opens once RPM drops to/below this
TURBO_VALVE_CONFIRM_SAMPLES  = 3       # consecutive reads required before opening (debounce)

# Pressure PID control
ARGON_FLUSH_FLOW_SETPOINT    = 150.0   # sccm — initial flow on flush entry
PRESSURE_CONTROL_KP          = 8.0     # sccm/V — proportional gain (tuned)
PRESSURE_CONTROL_KD          = 3.0     # sccm·s/V — derivative gain (tuned)
PRESSURE_CONTROL_KI          = 0.005   # sccm/(V·s) — integral gain
PRESSURE_CONTROL_ICLAMP      = 50.0    # sccm — anti-windup clamp (KI=0 is safe)

# Timing
PLASMA_IGNITION_TIMEOUT      = 120.0   # seconds — auto-abort if plasma not confirmed
POLLING_INTERVAL             = 0.2     # seconds between sensor reads
GUI_REFRESH_INTERVAL         = 200     # ms between GUI updates
ERROR_DISPLAY_SECONDS        = 10      # status-bar error auto-expiry

# MFC / DAC
MFC_FULL_SCALE               = 700.0   # sccm
MFC_GAS_CORRECTION_FACTOR    = 1.39    # Argon correction for MKS 1179A
ARGON_DAC_VREF               = 5.0
ARGON_DAC_RESOLUTION         = 4096

# Energy meter (PZEM-004T-100A, variac output — see Energy Meter section)
PZEM_SERIAL_PORT             = "/dev/ttyUSB0"
PZEM_SLAVE_ADDRESS           = 0xF8
PZEM_PLASMA_CURRENT_ON_A     = 1.0     # A — UNVALIDATED, bench-measure before trusting
PZEM_PLASMA_CURRENT_OFF_A    = 0.6     # A — hysteresis floor, must be < _ON_A
PZEM_PLASMA_CONFIRM_SAMPLES  = 3       # consecutive above-threshold reads to latch detection
```

### Tuning the Pressure PID Loop

Current tuned values (Kp=8, Kd=3) were arrived at empirically on hardware:

- Started at Kp=40 (original, P-only) — produced slow, large-amplitude oscillation
- Dropped to Kp=10 — oscillation reduced significantly but response was sluggish
- Raised to Kp=20, added Kd=3–7 — eliminated overshoot at the 0.09 mbar (ARGON_FLUSH) setpoint, but undershoot persisted at 0.007 mbar (SPUTTER_READY) since the same gains behave differently at very different flow regimes
- Settled at Kp=17→8 (further reduced after switching `POLLING_INTERVAL` from 0.5s to 0.2s, which made the derivative term ~2.5× more aggressive for the same physical Kd — **gains must be retuned whenever `POLLING_INTERVAL` changes**), Kd=7→3
- I-term added to address a small persistent offset; large Ki caused overshoot, kept small with anti-windup clamping (`PRESSURE_CONTROL_ICLAMP`). Setting Ki=0 while tuning is safe (no divide-by-zero).

If you change `POLLING_INTERVAL`, expect to retune Kd and Ki — both depend on `dt` between samples.

---

## GUI Guide

| Element | Description |
|---|---|
| **Pi IP** | Live IP address shown in header |
| **Process State** | Current state, colour-coded |
| **Safety Trip banner / Clear Fault** | Appears (red) in the Process State panel only when the global safety gate has forced a shutdown; see [Global Safety Gate](#global-safety-gate). Clearing does not fix the underlying condition — an unaddressed fault re-trips immediately |
| **Start Argon Flush** | Opens MFC valve, starts PID loop to 0.09 mbar |
| **Confirm Plasma** | Manually confirms plasma ignition; transitions to SPUTTER_READY. Highlights green once the PZEM confirms plasma-level current draw during PLASMA_IGNITING |
| **Auto-Confirm toggle** | Plasma panel. Off by default. When armed, a PZEM-confirmed detection auto-advances PLASMA_IGNITING → SPUTTER_READY without a click — see [Energy Meter](#energy-meter-pzem-004t-100a-plasma-ignition-sensing) |
| **PLASMA / PZEM readout / graph** | Plasma panel (replaces the old placeholder): live `plasma_detected` status, PZEM voltage/current/power/energy/frequency/power-factor, and one scrolling graph with a legend covering all but energy (shown as a numeric total instead) |
| **Start Sputter** | Begins sputtering from SPUTTER_READY |
| **Stop Sputter** | Ends sputtering, transitions directly to VENTING |
| **Vent** | Vents chamber to atmosphere |
| **Confirm Pump Off** | Hidden until atmospheric pressure is reached during VENTING; click completes the vent (closes the turbo inlet valve, transitions to IDLE) — see [Vent Completion Confirmation](#vent-completion-confirmation) |
| **E-STOP** | Immediate: kills flow, closes both valves (turbo valve by direct GPIO write — works even with a hung poll thread), drops opto, returns to IDLE and **latches**; Clear Fault to resume |
| **Voltage + Pressure (mbar)** | Live Pirani readings; mbar via log-linear calibration table |
| **OPTO** | Turbo Pump panel. Green = turbo enable opto on; Red = off |
| **T-VALVE** | Turbo Pump panel. Green `CLOSED` = inlet valve shut (normal); Orange `OPEN (venting)` = venting and turbo RPM has dropped to/below `TURBO_VALVE_OPEN_RPM_MAX` |
| **T-RPM / T-RPM V / turbo graph** | Own Turbo Pump panel (below Plasma, beside Pirani/MFC); turbo pump RPM (ADC A2), its raw ADC voltage, and a scrolling RPM graph, all read every tick |
| **Sputter P (mbar)** | Operator-set target pressure; press Set or Enter. Rejected (warning dialog) if ≤ 0 or > 0.05 mbar |
| **Argon PSI** | Operator-entered regulator pressure; ≥ 15 psi required for flush/sputter. Rejected (warning dialog) if < 15 psi |
| **Pirani graph** | Scrolling ADC voltage (lime, 0–4V, 60 samples) |
| **MFC graph** | Scrolling flow sccm (cyan) overlaid with DAC voltage (yellow dashed) |
| **DAC OUT** | Green = DAC found on I2C; Red = not detected |
| **Valve** | Green = released (MFC in control); Red = closed (emergency) |
| **Status bar** | Errors shown in red, auto-expire after 10 s |

---

## Known Limitations

- **Turbo enable opto (GPIO 17) is marginal**: the enable input draws ~15–30 mA, beyond a 4N35's ~10 mA saturated capability at legal GPIO LED drive. Currently only works with excess LED current. Proper fix (BC547 output buffer) designed but not yet installed.
- **Argon PSI guard is honor-system**: the ≥15 psi check reads an operator-entered value, not a sensor, and the entered value persists across runs. By design — this is a manual regulator reading, not something this rig senses directly.
- **No series protection resistors on ADC inputs yet** — recommended as general input protection.
- **`_ignite_plasma()` is a stub**: RF power supply trigger is not yet implemented.
- **PZEM plasma-detection thresholds are unvalidated placeholders** (`PZEM_PLASMA_CURRENT_ON_A`/`OFF_A`): guessed values, not yet measured against the real supply's no-load vs. struck-plasma current. This is why Auto-Confirm defaults off — see [Energy Meter](#energy-meter-pzem-004t-100a-plasma-ignition-sensing).
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
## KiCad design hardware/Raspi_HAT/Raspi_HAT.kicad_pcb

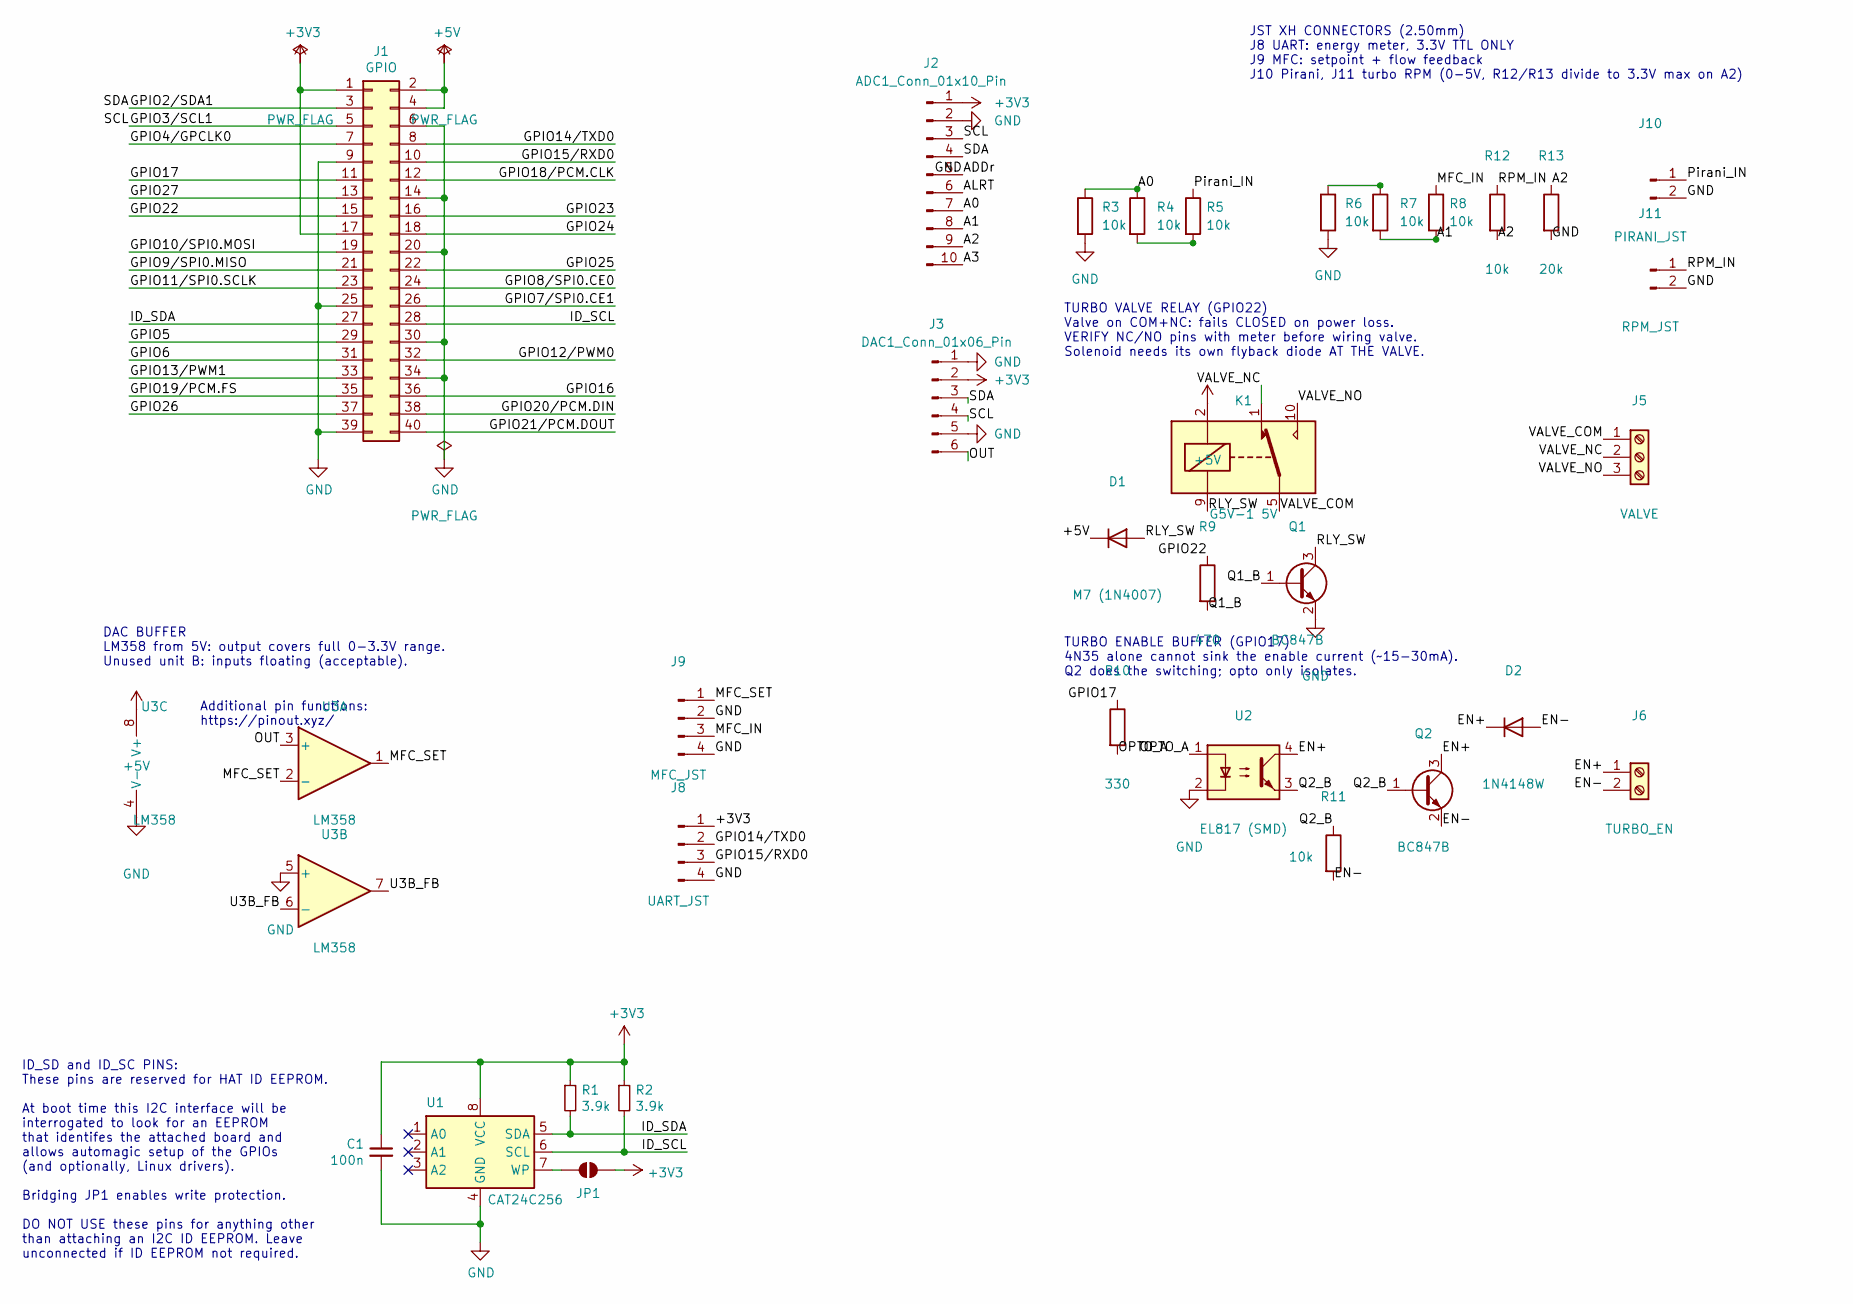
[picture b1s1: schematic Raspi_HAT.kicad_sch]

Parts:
C1: 100n; C_0805_2012Metric
D1: M7 (1N4007); D_SMA
D2: 1N4148W; D_SOD-123
J1: GPIO; PinSocket_2x20_P2.54mm_Vertical
J2: ADC1_Conn_01x10_Pin; PinSocket_1x10_P2.54mm_Vertical
J3: DAC1_Conn_01x06_Pin; PinSocket_1x06_P2.54mm_Vertical
J5: VALVE; TerminalBlock_Phoenix_MKDS-1,5-3-5.08_1x03_P5.08mm_Horizont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
J6: TURBO_EN; TerminalBlock_Phoenix_MKDS-1,5-2-5.08_1x02_P5.08mm_Horizont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
J8: UART_JST; JST_XH_B4B-XH-A_1x04_P2.50mm_Vertical
J9: MFC_JST; JST_XH_B4B-XH-A_1x04_P2.50mm_Vertical
J10: PIRANI_JST; JST_XH_B2B-XH-A_1x02_P2.50mm_Vertical
J11: RPM_JST; JST_XH_B2B-XH-A_1x02_P2.50mm_Vertical
JP1: ID_WP; SolderJumper-2_P1.3mm_Open_TrianglePad1.0x1.5mm
K1: G5V-1 5V; Relay_SPDT_Omron_G5V-1
Q1, Q2: BC847B; SOT-23
R1, R2: 3.9k; R_0805_2012Metric
R3, R4, R5, R6, R7, R8, R11, R12: 10k; R_0805_2012Metric
R9: 470; R_0805_2012Metric
R10: 330; R_0805_2012Metric
R13: 20k; R_0805_2012Metric
U1: CAT24C256; SOIC-8_3.9x4.9mm_P1.27mm
U2: EL817 (SMD); SO-4_7.6x3.6mm_P2.54mm
U3: LM358; SOIC-8_3.9x4.9mm_P1.27mm

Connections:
+3V3: C1.1, J1.1, J1.17, J2.1, J3.2, J8.1, JP1.2 (B), R1.1, R2.1, U1.8 (VCC)
+5V: D1.1 (K), J1.2, J1.4, K1.2, U3.8 (V+)
/A0: J2.7, R3.1, R4.1
/A1: J2.8, R7.2, R8.2
/A2: J2.9, R12.2, R13.1
/A3: J2.10
/ALRT: J2.6
/EN+: D2.1 (K), J6.1, Q2.3 (C), U2.4
/EN-: D2.2 (A), J6.2, Q2.2 (E), R11.2
/GPIO2/SDA1: J1.3, J2.4, J3.3
/GPIO3/SCL1: J1.5, J2.3, J3.4
/GPIO4/GPCLK0: J1.7
/GPIO5: J1.29
/GPIO6: J1.31
/GPIO7/SPI0.CE1: J1.26
/GPIO8/SPI0.CE0: J1.24
/GPIO9/SPI0.MISO: J1.21
/GPIO10/SPI0.MOSI: J1.19
/GPIO11/SPI0.SCLK: J1.23
/GPIO12/PWM0: J1.32
/GPIO13/PWM1: J1.33
/GPIO14/TXD0: J1.8, J8.2
/GPIO15/RXD0: J1.10, J8.3
/GPIO16: J1.36
/GPIO17: J1.11, R10.1
/GPIO18/PCM.CLK: J1.12
/GPIO19/PCM.FS: J1.35
/GPIO20/PCM.DIN: J1.38
/GPIO21/PCM.DOUT: J1.40
/GPIO22: J1.15, R9.1
/GPIO23: J1.16
/GPIO24: J1.18
/GPIO25: J1.22
/GPIO26: J1.37
/GPIO27: J1.13
/ID_SCL: J1.28, R2.2, U1.6 (SCL)
/ID_SDA: J1.27, R1.2, U1.5 (SDA)
/MFC_IN: J9.3, R8.1
/MFC_SET: J9.1, U3.1, U3.2 (-)
/OPTO_A: R10.2, U2.1
/OUT: J3.6, U3.3 (+)
/Pirani_IN: J10.1, R5.1
/Q1_B: Q1.1 (B), R9.2
/Q2_B: Q2.1 (B), R11.1, U2.3
/RLY_SW: D1.2 (A), K1.9, Q1.3 (C)
/RPM_IN: J11.1, R12.1
/U3B_FB: U3.6 (-), U3.7
/VALVE_COM: J5.1, K1.5, K1.6
/VALVE_NC: J5.2, K1.1
/VALVE_NO: J5.3, K1.10
GND: C1.2, J1.6, J1.9, J1.14, J1.20, J1.25, J1.30, J1.34, J1.39, J2.2, J2.5, J3.1, J3.5, J8.4, J9.2, J9.4, J10.2, J11.2, Q1.2 (E), R3.2, R6.2, R13.2, U1.4 (GND), U2.2, U3.4 (V-), U3.5 (+)
unnamed: JP1.1 (A), U1.7 (WP)
unnamed: R4.2, R5.2
unnamed: R6.1, R7.1

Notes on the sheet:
Additional pin functions: https://pinout.xyz/
TURBO ENABLE BUFFER (GPIO17) 4N35 alone cannot sink the enable current (~15-30mA). Q2 does the switching; opto only isolates.
ID_SD and ID_SC PINS: These pins are reserved for HAT ID EEPROM. At boot time this I2C interface will be interrogated to look for an EEPROM that identifes the attached board and allows automagic setup of the GPIOs (and optionally, Linux drivers). Bridging JP1 enables write protection. DO NOT USE th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
JST XH CONNECTORS (2.50mm) J8 UART: energy meter, 3.3V TTL ONLY J9 MFC: setpoint + flow feedback J10 Pirani, J11 turbo RPM (0-5V, R12/R13 divide to 3.3V max on A2)
TURBO VALVE RELAY (GPIO22) Valve on COM+NC: fails CLOSED on power loss. VERIFY NC/NO pins with meter before wiring valve. Solenoid needs its own flyback diode AT THE VALVE.
DAC BUFFER LM358 from 5V: output covers full 0-3.3V range. Unused unit B: inputs floating (acceptable).

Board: 2 copper layers, 36 parts (1 on the bottom side), 32 nets, no tracks yet.

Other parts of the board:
MH1, MH2, MH3, MH4: MountingHole_2.7mm_M2.5

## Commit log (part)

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2026-06-10 fixed some venv issues
2026-06-10 added setup.sh
2026-06-11 added graphs for pirani and mfc
2026-06-13 Add config.py and refactor sputter workflow with argon flush and plasma stages
    - added centralized config.py for ADC/DAC addresses, thresholds, and GUI settings
    - added ARGON_FLUSH, PLASMA_IGNITING, and SPUTTER_READY workflow states
    - restored Start Sputter button while keeping argon flush separate
    - introduced placeholder plasma UI pane and _ignite_plasma() stub
    - added MFC DAC/flow placeholders and argon flush pressure handling
    - updated state/button logic and status messaging for new stages
2026-06-18 added mfc flow rate and dac output graphs overlapping
2026-06-20 added proportional control for pressure using the actuation of mfc
2026-06-20 removed venv and __pychache__ and updated .gitignore
2026-06-20 Created README.md
2026-06-21 Update README.md
    added setup instructions
2026-06-21 updated config.py with tuned values of kp and kd for the control loop
2026-06-25 sputter pressure target input, pirani cal table interpolation, venting at 2.5V, clean shutdown
2026-06-25 PID control, log-linear pirani interpolation, sputter pressure input, clean shutdown, UI fixes
